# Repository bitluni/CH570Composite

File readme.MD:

# CH570 Composite

This project uses the CH570 chip to generate a PAL video signal. It appears as a CDC device. Text sent over serial will be displayed on the screen "^L" clears the screen.

./pcb contains the design files
./tools contain helper tools (AI generated)

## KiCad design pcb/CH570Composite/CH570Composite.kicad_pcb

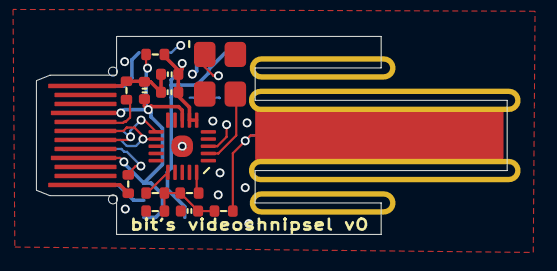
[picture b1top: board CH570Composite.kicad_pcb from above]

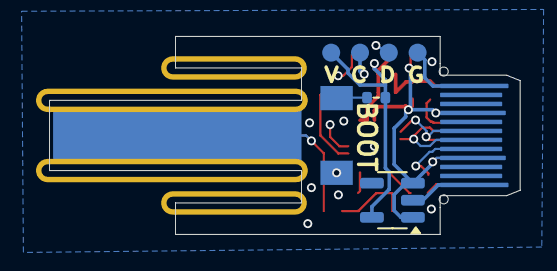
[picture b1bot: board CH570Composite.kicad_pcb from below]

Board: 4 copper layers, 26.2 x 11.0 mm, 19 parts (4 on the bottom side), 14 nets.

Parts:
C1, C3: 2.2u; C_0402_1005Metric
C2: 100n; C_0402_1005Metric
C4: C_0402_1005Metric
LS1: RCA; RCA PCB
R1, R2, R7: 5.1k; R_0402_1005Metric
R3, R5, R6, R8: R_0402_1005Metric
R4: 1.5k; R_0402_1005Metric
SW1: miniButton
TP1: TestPoint; Testpoint4_small
U1: CH572D; QFN-20-1EP_3x3mm_P0.4mm_EP1.65x1.65mm
U2: PCB USB-C (Aisler)
U3: SOT-23-5
Y1: Crystal_GND24; Crystal_SMD_3225-4Pin_3.2x2.5mm

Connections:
+3.3V: C2.1, C3.2, R4.1, R7.2, TP1.4, U1.6 (VDD33), U1.7 (VIO33), U3.5 (VOUT)
+5V: C1.1, R4.2, U1.8 (V5), U2.A4 (VBUS), U2.A9 (VBUS), U2.B4 (VBUS), U2.B9 (VBUS), U3.1 (VIN), U3.3 (CE)
A0: TP1.2, U1.11 (PA0/UDM/R2/T3/SCL1), U2.A7 (D-), U2.B7 (D-)
A1: SW1.1, TP1.3, U1.12 (PA1/UDP/R3/T2/SDA1), U2.A6 (D+), U2.B6 (D+)
A2: R8.2, U1.20 (PA2/R/T1/SDA2/SCS_/PWM2/TMR1/CN)
A7: R3.1, U1.16 (PA7/MOSI/T4/PWM1/TMR/RST_/CP1)
GND: C1.2, C2.2, C3.1, C4.2, LS1.2 (GND), R1.2, R2.2, R6.1, TP1.1, U1.21 (VSS), U2.A1 (GND), U2.A12 (GND), U2.B1 (GND), U2.B12 (GND), U3.2 (VSS), Y1.2, Y1.4
unnamed: C4.1, R3.2, R5.1, R6.2, R8.1
unnamed: R7.1, SW1.2
unnamed: R2.1, U2.A5 (CC1)
unnamed: R1.1, U2.B5 (CC2)
VIDEO: LS1.1 (S), R5.2
XI: U1.3 (XI), Y1.1
XO: U1.2 (XO), Y1.3
